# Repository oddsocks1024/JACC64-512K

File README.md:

# JACC64-512K

## Description
JACC64-512K: Just Another Commodore Cartridge.

A cartridge for the Commodore 64 that holds 32 selectable 16K ROM images

**Additional Features**
* Power LED
* Reset Switch

## Bill of Materials

| Qty | Component                              |
|:---:|----------------------------------------|
| 1   | 5mm LED                                |
| 1   | 6mm Tactile Push Button                |
| 1   | 330Ω Axial Resistor - ¼ watt (LED)     |
| 6   | 10KΩ Axial Resistors - ¼ watt          |
| 2   | 1N4148 Diodes                          |
| 1   | 100nF Ceramic Capacitor                |
| 1   | 5-pole DIP Switch                      |
| 1   | SST39SF040 EEPROM (or compatible)      |

* IC sockets optional
* The LED resistor is nominally 330Ω but anything up to 1K is fine
* You will need to join 32 x 16K ROM images together into a single image before burning to the EEPROM
* Smaller EEPROMs could be used, but will obviously hold fewer images and the DIP switch should be set accordingly

## 3D Printable Case
A 3D printable case specifically designed for this PCB is also available. STLs are included in this repo and there is also a [Thingiverse Page](https://www.thingiverse.com/thing:7089362)

* Designed to use screws as they produce a much nicer, more robust case
* 2 x 3.5mm self-tapping screws to attach the shells. Max length about 15mm

## Support Me
* [My Projects](https://projects.amiga-hardware.com) - Donate on this page
* [Order the JACC64-512K PCB](https://www.pcbway.com/project/shareproject/JACC64_512K_32_Game_C64_Cartridge_42f2de5b.html)
* [Order the JACC64-512K Case](https://www.pcbway.com/project/shareproject/JACC64_512K_C64_Cartridge_Case_49b9f140.html)

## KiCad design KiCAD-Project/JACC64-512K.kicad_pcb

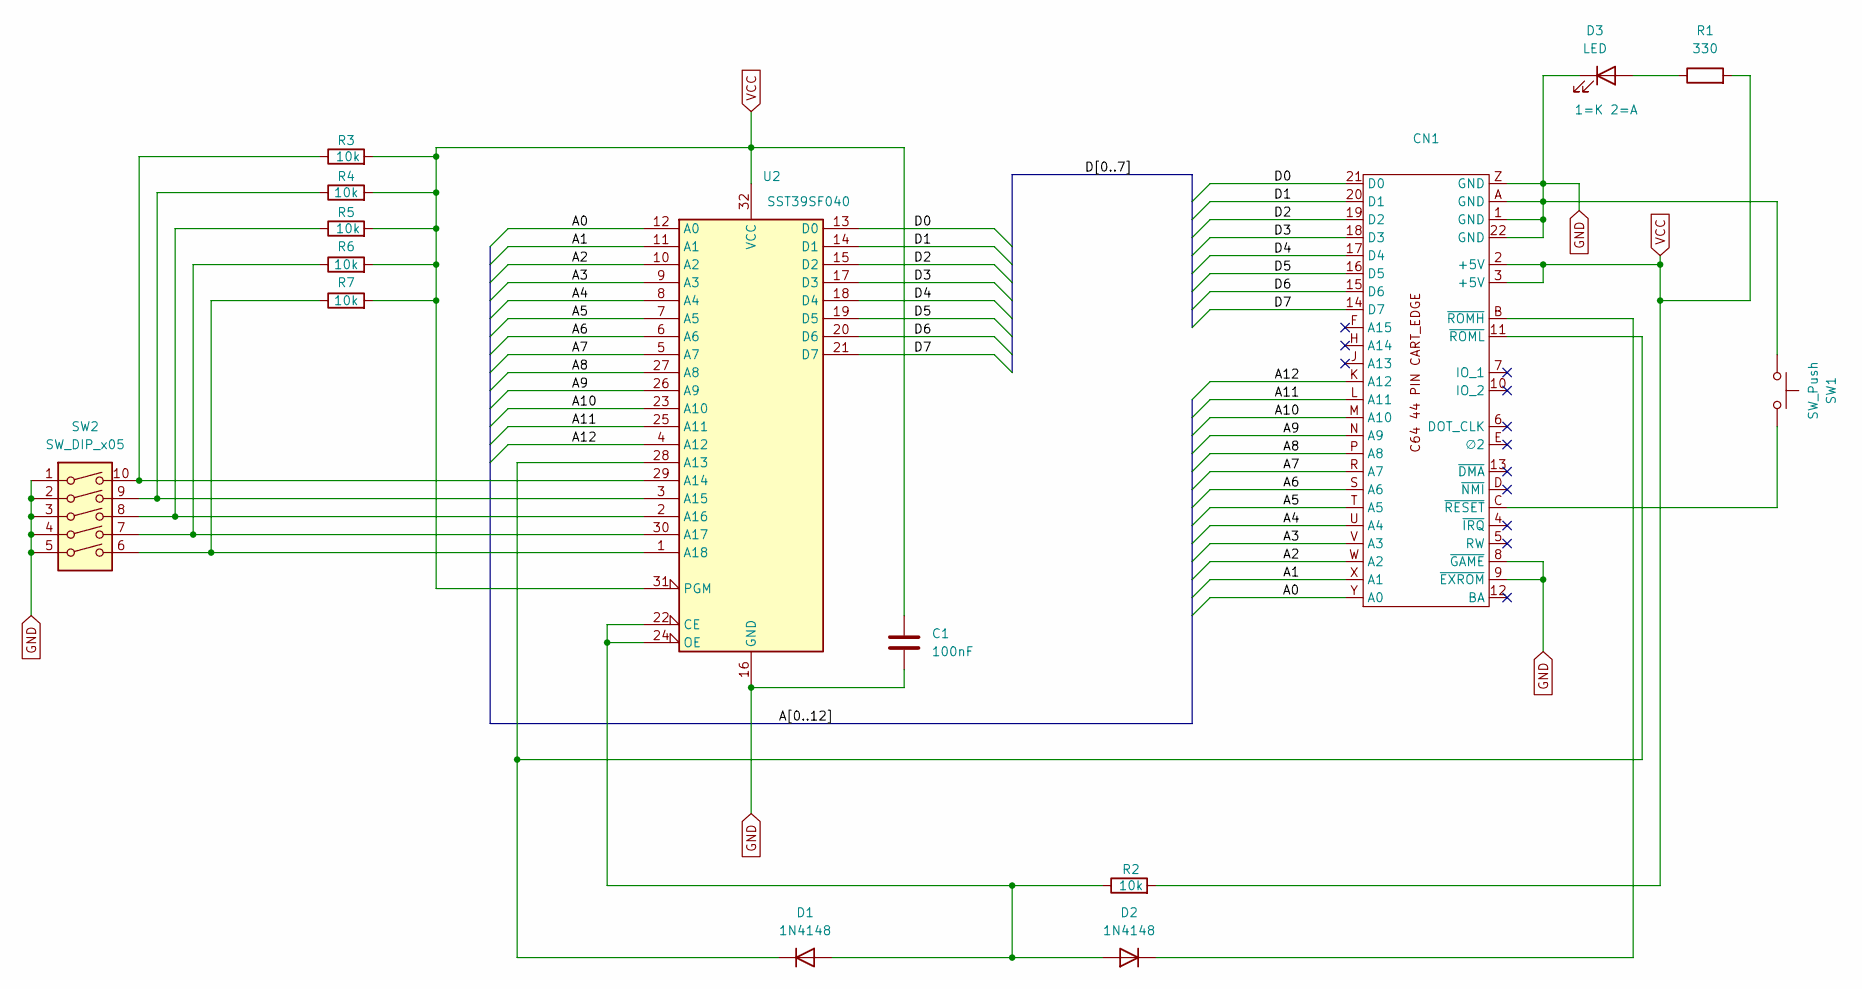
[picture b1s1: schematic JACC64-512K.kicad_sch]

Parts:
C1: 100nF; C_Disc_D5.0mm_W2.5mm_P5.00mm
CN1: C64 Expansion
D1, D2: 1N4148; D_DO-41_SOD81_P7.62mm_Horizontal
D3: LED; LED_D5.0mm
R1: 330; R_Axial_DIN0207_L6.3mm_D2.5mm_P10.16mm_Horizontal
R2, R3, R4, R5, R6, R7: 10k; R_Axial_DIN0207_L6.3mm_D2.5mm_P10.16mm_Horizontal
SW1: SW_Push; SW_PUSH_6mm
SW2: SW_DIP_x05; SW_DIP_SPSTx05_Slide_9.78x14.88mm_W7.62mm_P2.54mm
U2: SST39SF040; DIP-32_W15.24mm

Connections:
/A0: CN1.Y (A0), U2.12 (A0)
/A1: CN1.X (A1), U2.11 (A1)
/A2: CN1.W (A2), U2.10 (A2)
/A3: CN1.V (A3), U2.9 (A3)
/A4: CN1.U (A4), U2.8 (A4)
/A5: CN1.T (A5), U2.7 (A5)
/A6: CN1.S (A6), U2.6 (A6)
/A7: CN1.R (A7), U2.5 (A7)
/A8: CN1.P (A8), U2.27 (A8)
/A9: CN1.N (A9), U2.26 (A9)
/A10: CN1.M (A10), U2.23 (A10)
/A11: CN1.L (A11), U2.25 (A11)
/A12: CN1.K (A12), U2.4 (A12)
/D0: CN1.21 (D0), U2.13 (D0)
/D1: CN1.20 (D1), U2.14 (D1)
/D2: CN1.19 (D2), U2.15 (D2)
/D3: CN1.18 (D3), U2.17 (D3)
/D4: CN1.17 (D4), U2.18 (D4)
/D5: CN1.16 (D5), U2.19 (D5)
/D6: CN1.15 (D6), U2.20 (D6)
/D7: CN1.14 (D7), U2.21 (D7)
GND: C1.1, CN1.1 (GND), CN1.8 (~GAME), CN1.9 (~EXROM), CN1.22 (GND), CN1.A (GND), CN1.Z (GND), D3.1 (K), SW1.1, SW2.1, SW2.2, SW2.3, SW2.4, SW2.5, U2.16 (GND)
unnamed: CN1.C (~RESET), SW1.2
unnamed: CN1.B (~ROMH), D2.1 (K)
unnamed: CN1.11 (~ROML), D1.1 (K), U2.28 (A13)
unnamed: D1.2 (A), D2.2 (A), R2.1, U2.22 (CE), U2.24 (OE)
unnamed: D3.2 (A), R1.1
unnamed: R3.1, SW2.10, U2.29 (A14)
unnamed: R4.1, SW2.9, U2.3 (A15)
unnamed: R5.1, SW2.8, U2.2 (A16)
unnamed: R6.1, SW2.7, U2.30 (A17)
unnamed: R7.1, SW2.6, U2.1 (A18)
VCC: C1.2, CN1.2 (+5V), CN1.3 (+5V), R1.2, R2.2, R3.2, R4.2, R5.2, R6.2, R7.2, U2.31 (PGM), U2.32 (VCC)

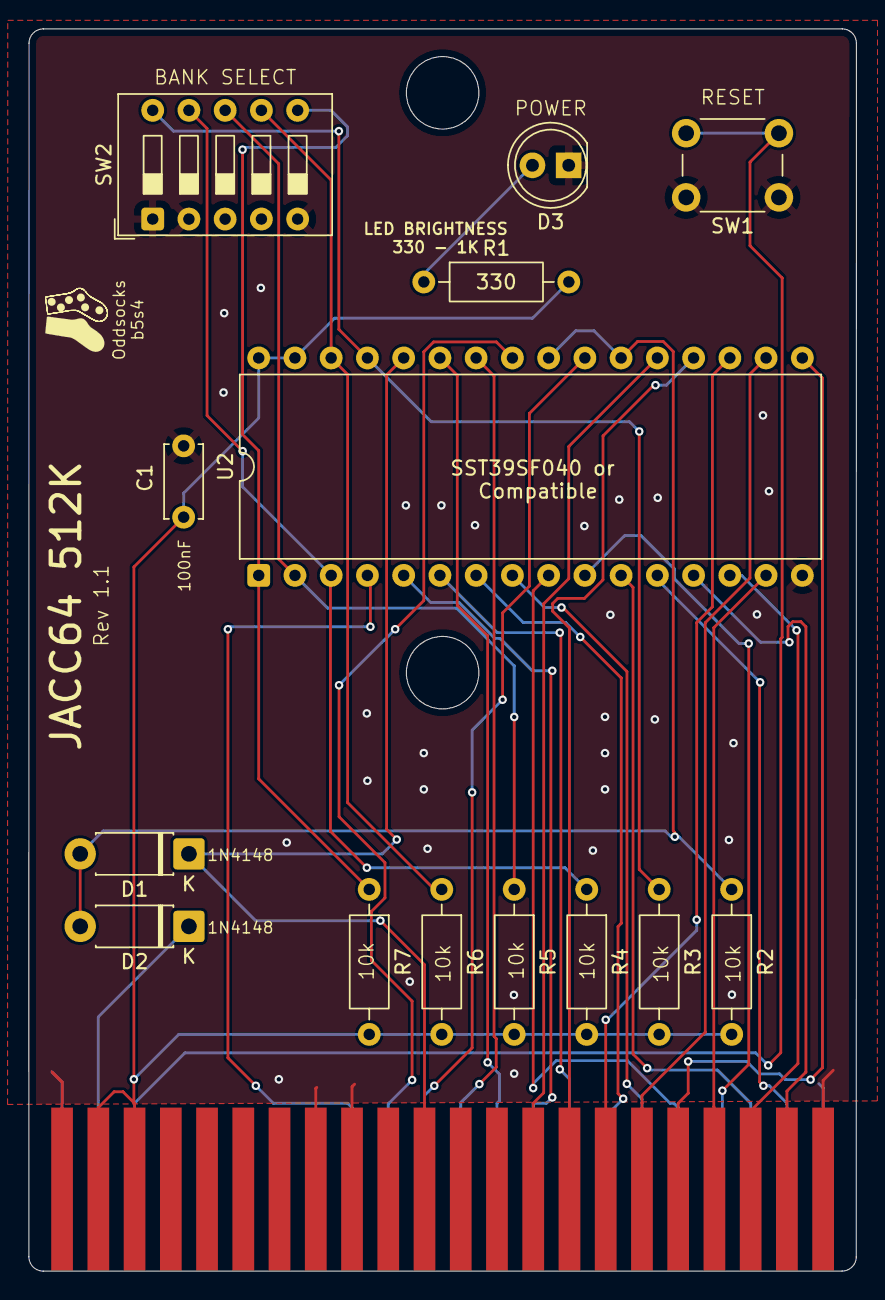
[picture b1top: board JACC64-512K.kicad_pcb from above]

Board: 2 copper layers, 58.0 x 87.1 mm, 15 parts (0 on the bottom side), 33 nets.

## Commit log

2025-11-09 Added gerbers and updated README.md
2025-11-29 Added PDF schematics
2025-11-30 Add license file
